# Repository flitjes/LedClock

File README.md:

A project for creating ledclock. 
The project contains the source for the actual clock and is depended
on a couple of breakouts, RTC, LDR and PIR.

This is tied together with an msp430g2553 to display the time on a ledclock
and be energy sufficient.

Besides the software I've made a 3D drawing which will be milled out of a mix
of materials, plexiglas, carbonfiber and MDF.

Protocol:
Set the time
time=12:10:04
start

setcolor=[id][rgb code]
id 0 = HOUR
id 1 = MINUTE
id 2 = SECOND (not implemented)
id 3 = BACKGROUND (not implemented)

Set the color
setcolor=0ffddff
start

Example with netcat
nc -u 192.168.4.1 12345
setcolor=0ff00ff

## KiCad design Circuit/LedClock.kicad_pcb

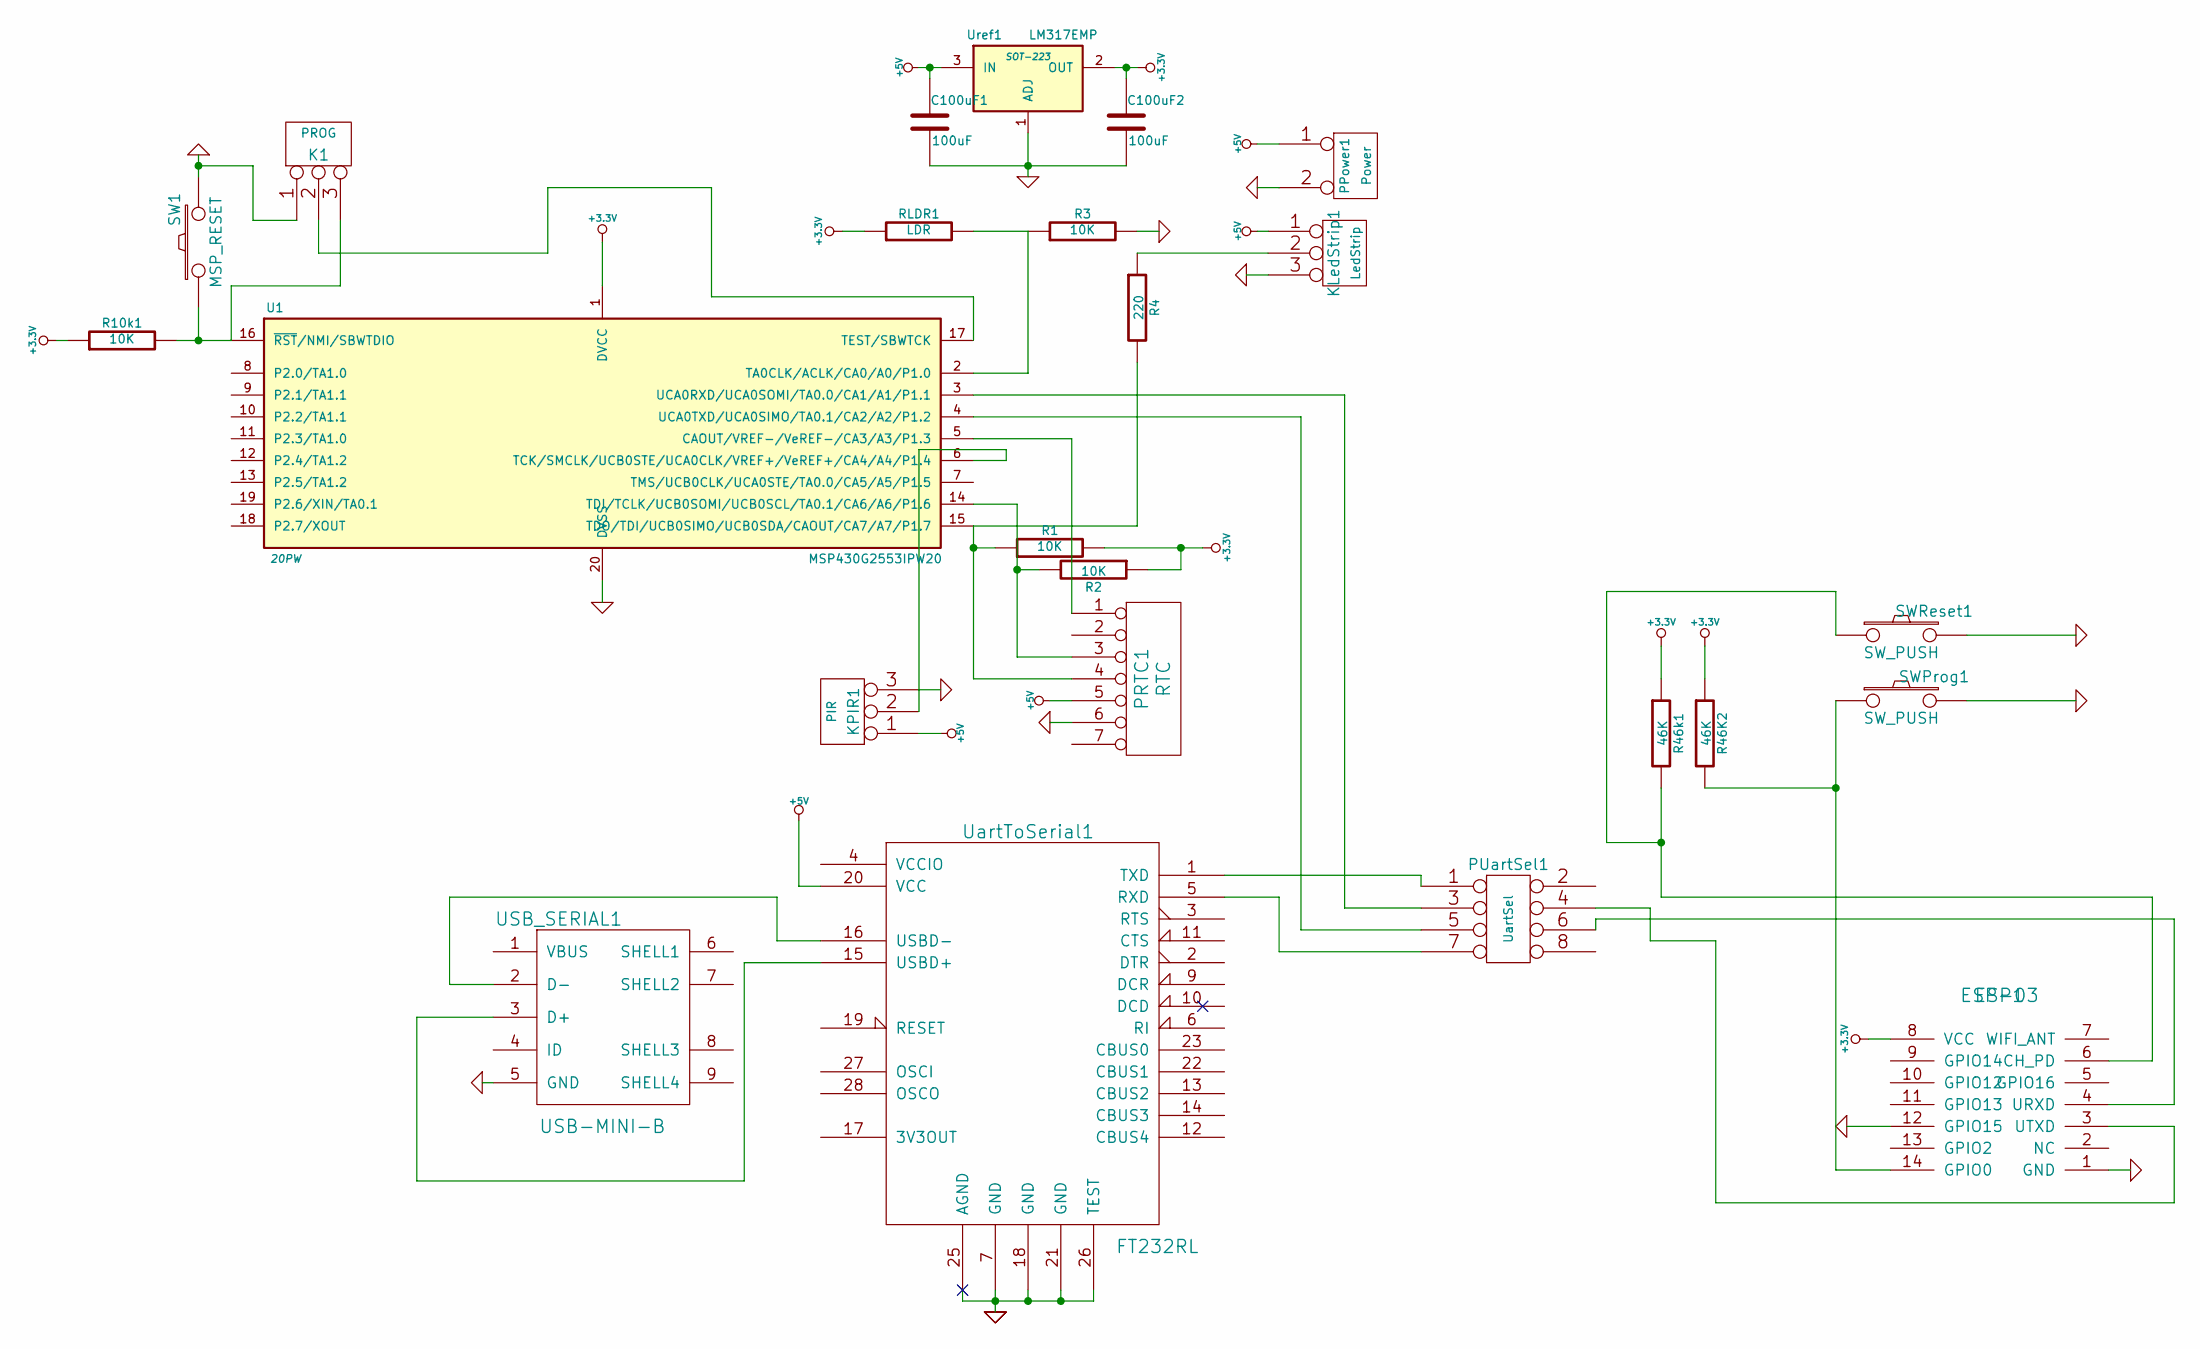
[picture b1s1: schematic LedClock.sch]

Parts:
C100uF1, C100uF2: 100uF
ESP1: ESP-03
K1: PROG
KLedStrip1: LedStrip
KPIR1: PIR
PPower1: Power
PRTC1: RTC
PUartSel1: UartSel
R1, R2, R3, R10k1: 10K
R4: 220
R46K2, R46k1: 46K
RLDR1: LDR
SW1: MSP_RESET
SWProg1: SW_PUSH
SWReset1: SW_PUSH
U1: MSP430G2553IPW20; 20PW
USB_SERIAL1: USB-MINI-B
UartToSerial1: FT232RL
Uref1: LM317EMP; SOT-223

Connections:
+3.3V: C100uF2.1, ESP1.8 (VCC), R1.2, R2.1, R10k1.1, R46K2.1, R46k1.1, RLDR1.1, U1.1 (DVCC), Uref1.2 (OUT)
+5V: C100uF1.1, KLedStrip1.1, KPIR1.1, PPower1.1, PRTC1.5, UartToSerial1.20 (VCC), Uref1.3 (IN)
GND: C100uF1.2, C100uF2.2, ESP1.1 (GND), ESP1.12 (GPIO15), K1.1, KLedStrip1.3, KPIR1.3, PPower1.2 (PM), PRTC1.6, R3.2, SW1.2, SWProg1.2, SWReset1.2, U1.20 (DVSS), USB_SERIAL1.5 (GND), UartToSerial1.7 (GND), UartToSerial1.18 (GND), UartToSerial1.21 (GND), UartToSerial1.25 (AGND), UartToSerial1.26 (TEST), Uref1.1 (ADJ)
unnamed: USB_SERIAL1.3 (D+), UartToSerial1.15 (USBD+)
unnamed: PUartSel1.7, UartToSerial1.5 (RXD)
unnamed: R3.1, RLDR1.2, U1.2 (TA0CLK/ACLK/CA0/A0/P1.0)
unnamed: KPIR1.2 (PM), U1.6 (TCK/SMCLK/UCB0STE/UCA0CLK/VREF+/VeREF+/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)
unnamed: PUartSel1.1, UartToSerial1.1 (TXD)
unnamed: PUartSel1.3, U1.3 (UCA0RXD/UCA0SOMI/TA0.0/CA1/A1/P1.1)
unnamed: PUartSel1.5, U1.4 (UCA0TXD/UCA0SIMO/TA0.1/CA2/A2/P1.2)
unnamed: USB_SERIAL1.2 (D-), UartToSerial1.16 (USBD-)
unnamed: PRTC1.1, U1.5 (CAOUT/VREF-/VeREF-/CA3/A3/P1.3)
unnamed: KLedStrip1.2 (PM), R4.1
unnamed: K1.3, R10k1.2, SW1.1, U1.16 (~RST~/NMI/SBWTDIO)
unnamed: K1.2 (PM), U1.17 (TEST/SBWTCK)
unnamed: ESP1.14 (GPIO0), R46K2.2, SWProg1.1
unnamed: ESP1.6 (CH_PD), R46k1.2, SWReset1.1
unnamed: ESP1.4 (URXD), PUartSel1.6
unnamed: ESP1.3 (UTXD), PUartSel1.4
unnamed: PRTC1.4, R1.1, R4.2, U1.15 (TDO/TDI/UCB0SIMO/UCB0SDA/CAOUT/CA7/A7/P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)
unnamed: PRTC1.3, R2.2, U1.14 (TDI/TCLK/UCB0SOMI/UCB0SCL/TA0.1/CA6/A6/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)

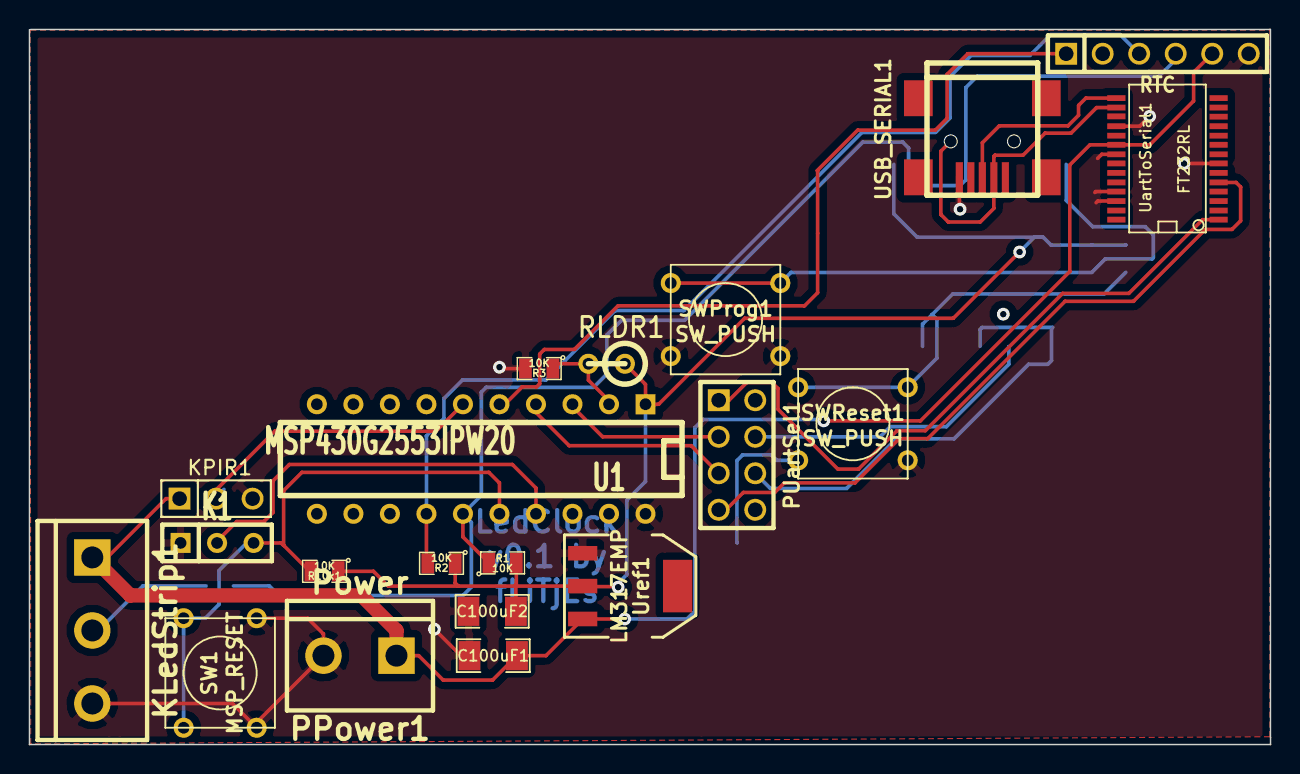
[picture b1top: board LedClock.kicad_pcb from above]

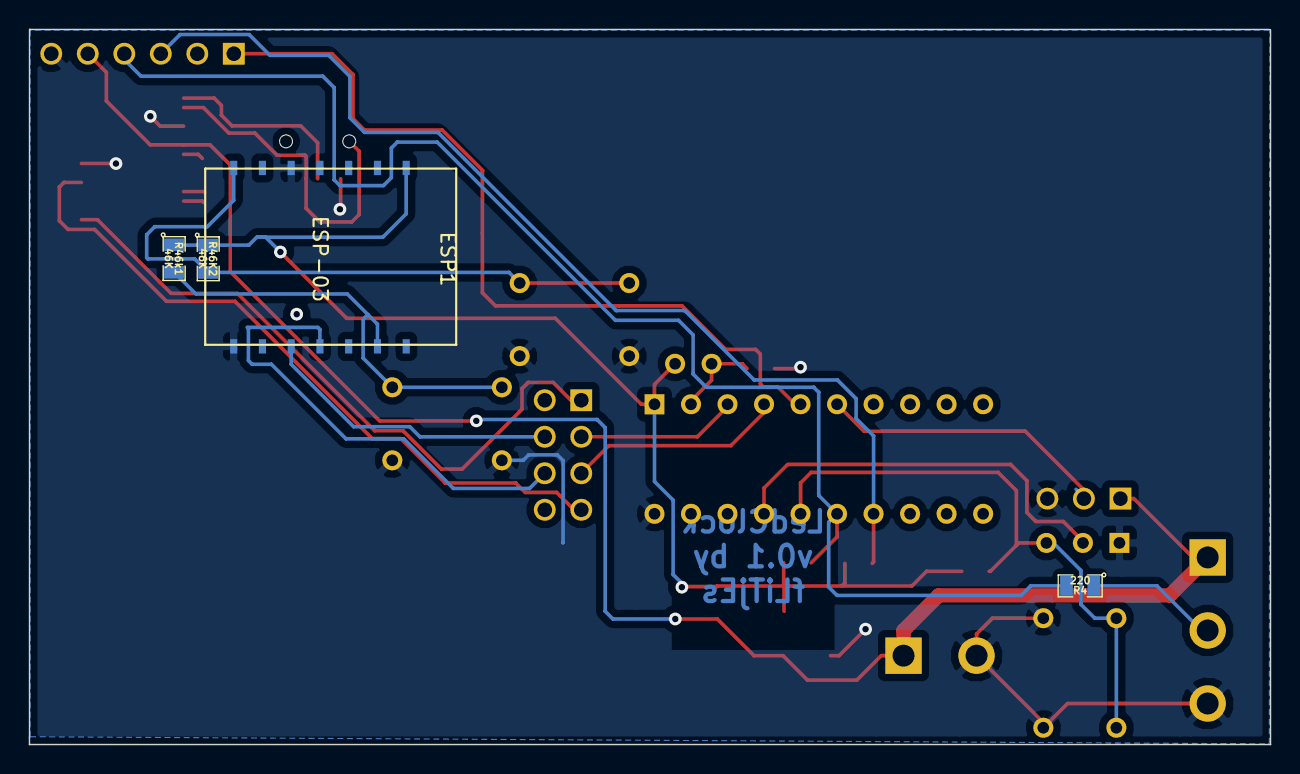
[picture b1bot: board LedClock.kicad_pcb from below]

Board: 2 copper layers, 86.3 x 49.7 mm, 24 parts (4 on the bottom side), 21 nets.

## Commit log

2015-07-12 Updated with statemachine
2015-07-12 Fixed animation birghtness of trailing leds
2015-07-12 Added brightness control Removed the amount of leds from the animation call
2015-07-25 Enabled dynamic brightness controll based on an LDR connected to the ADC channel 0 on P1.0
2015-07-25 Moved debug related code to debug.h
2015-07-25 Fixed 3 pin mode initalisation for SPI
2015-07-25 Fixed SPI init in ws2812.c Adding ADC and USCI_B0 and debug.h forgot those in previous commits..
2015-07-25 added git ignore files to prevent Debug and generated grace stuff to get in git
2015-07-25 Removed all unneccesary config and debug files from the repo
2015-07-25 Updated .gitignore to ignore previously removed files for future commits
2015-07-25 Added grace.lib
2015-07-26 Added multiplex pin P2.5 to controll the mux for switching SDA between I2C devices and ws2812
    P2.5
    high == ws2812 low == I2C bus
2015-08-04 Added I2C and RTC support Reading and writing to I2C work HW support for toggling is not in place yet Printing of current time is incorrect
2015-08-04 Updated driver with only setting and clearing bits instead of wiping out the entire register..
2015-08-12 Added cad drawing, in progress
2015-08-22 Set time will set the of the RTC as well
2015-08-23 Added led offset for led 0, incase the ledstrip is mounted not as expected
2015-08-23 Added state history and switching function. Introduced new state logging. Added print time feature
2015-08-23 Removed pin toggle for switching spi and i2c, not necessary any more. Disabled debug
2015-08-23 Led clock will start after init
2015-08-23 I2C read write wrappers added
2015-08-23 Added hardware abstraction layer and enabled set squarewave output
2015-08-23 Changed from internal timer to external I/O from RTC
2015-08-23 Cleaned up old timer code
2015-08-23 Human presence detection with PIR.
2015-08-24 Found bug, time was standing still when the leds where off...
2015-08-24 Updated ledclock design. Made primitive objects for the cuttouts.
2015-08-29 Updated animation brightness control and let the animation run in a circular fashion
2015-09-03 Added gamma correction and base brighness value
2015-09-04 Added schematic and boardlayout
2015-09-04 Added Readme
2015-09-05 Added current limiting resistor on the ledstrip data line Adviced by adafruit
2015-09-05 Updated cad drawing based on actual pcb sizes
2015-09-06 Changed git submodules for open-esp-sdk by moving them a folder upwards
2015-09-06 Updated git modules for esphttpd submodules
2015-09-06 Added pre-build open-esp-sdk
2015-09-06 Updated the use of _t types
2015-09-06 Added setup file for setting up build enviroment
2015-09-08 Updated clock prototype after lasercutting
2015-09-13 Moving average implemented for LDR controll
2015-09-13 Start stop feature broke after swap to gpio interrupt. Fixed it now.
2015-09-13 After restarting the clock it would jump back in time. Now it fetches the latest time from the rtc.
2015-09-14 Added data transfer option Disabled moving average, calculation should be moved to a timer Initialised ws2812 Added show data state
2015-09-15 Fixed clock not turning on after PIR timeout
2015-09-15 Added python test script to output test data on serial port
2015-09-26 Updated layout to fit the new ring and stay within 10*5cm
2015-09-26 Added GPL3 license
2015-09-26 Added set color mechanism for the clock
2015-09-27 Updated pcb w.r.t design rules and unconnected parts
2015-09-27 Updated width of power line accoording to spec
2015-09-29 Changed clock width
2015-10-12 Updated ledclock and sperrated everything in parts
2015-10-12 Updated test
2015-10-12 Removed commented default values
2015-10-12 Revert "Removed commented default values"
    This reverts commit 6a37c44d4b0144f7c01ff915d57850a3c0bc1299.
2015-10-12 Added Gerbers
2015-10-12 Updated schematic
2015-10-12 Separte modules are exported as parts
2015-10-12 Base with cutouts
2015-10-12 Updated parts and design with correct placements
2015-12-01 Fixed newline support, minicom goes with CR by default... now handling both
2015-12-30 Updated animation to show an anlog clock
2015-12-30 Animation fix
2015-12-30 Disabled serial echo
2015-12-30 Fixed timer issue, could count past 60 if timer interrupt interrupted ticking. Moved moving average to seperate interrupt handler, no need to calculate the brightness every second
2016-01-08 Updted design
2016-01-11 Updated pcb with cutting edges, fixed minor issue and put name and version on pcb
2016-01-21 changed setting led strip with certain length to handle a circle
2016-01-21 Added struct to 32bit convertion functions as prep for gradient calculations
2016-01-23 Added generated gcode. Diffuser is done by hand partially.
2016-01-31 Fixed 24 hour input, will be transformed to 12 hour format
2016-01-31 Moved clock handling outside of interrupt handler Updating every modulo 10 of a second
2016-01-31 Added gradient support, updated display interval and set default gradient level to 50 procent
2016-02-04 Moved interrupt handlers from main into vector.c because naming changed.. Fixed 24 hour format because 12 was not the correct value
2016-02-04 Updated animation with clear spots indicating the arrows and changed the interrupt handlig inside the vector
2016-02-20 Updated pcb layout and circuit, found 1 flaw in the design
2016-02-22 Fixed setting color and moved the LED offset by 1 for current install. After fresh IDE install some stuff is updated
2016-03-01 Removed unused esp related stuff
2016-03-01 Updated 3d model to be thinner and added magnet pockets and ldr pocket
2016-04-27 Added stl's for easy code generation and added magnet holes to old design
2016-07-24 Adding folder for App to be stored on git
2016-07-24 Adding the project manually because Android Studio has no support for push a project to an existing repo
2017-02-18 Added udp protocol
2017-02-18 Update README.md
    Updated
